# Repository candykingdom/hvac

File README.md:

# Playa engineering!

## Installing the breadboard in arduino

You have to install the board type "atmega328 on a breadboard". Follow the
instructions in [Minimal Circuit (Eliminating the External
Clock)](https://www.arduino.cc/en/Tutorial/ArduinoToBreadboard)

## Digikey components

Power:

[Sabre flat blade literature](http://www.literature.molex.com/SQLImages/kelmscott/Molex/PDF_Images/987650-5662.PDF)

For a 10 foot run @ 12v 4A, allowing for 3% voltage drop.

Wire Size           14 AWG
Voltage at Max Drop 11.64 V

 *  [Board Side](https://www.digikey.com/product-detail/en/molex-llc/0431601102/WM18483-ND/300116)
 *  [Cable Side](https://www.digikey.com/products/en?keywords=44441-2002)
 *  [Crimp](https://www.digikey.com/product-detail/en/molex-llc/0433750001/WM9174CT-ND/300126)

Motors:
 *  [Board Side](http://www.mouser.com/ProductDetail/Molex/43160-3106/?qs=sGAEpiMZZMs%252bGHln7q6pm%252bS0pk2Wo0XxzlBm66UhqE8%3d)
 *  [Cable Side](https://www.digikey.com/product-detail/en/molex-llc/0444412006/WM18467-ND/300100) # Find the cable side version
 *  Same crimps

Data:

 *  [Board Side](https://www.digikey.com/short/3nbvwp)
 *  [Cable Side](https://www.digikey.com/product-detail/en/molex-llc/0511030900/WM13237-ND/3262504)
 *  [Crimp](https://www.digikey.com/product-detail/en/molex-llc/0503518000/WM3320CT-ND/2405712)

More components:

 *  [Through hole potentiometer](https://www.digikey.com/product-detail/en/bourns-inc/PDB12-H4301-103BF/PDB12-H4301-103BF-ND/3780664)
 *  [Through hole toggle switch](https://www.digikey.com/product-detail/en/e-switch/100SP1T1B4M2QE/EG2355-ND/378824)
 *  [Pushbutton Switch (PVA-H2)](https://www.digikey.com/product-detail/en/c-k/Y17P12211FP/401-1135-ND/417718)
 *  [MOSFET](https://www.digikey.com/product-detail/en/nexperia-usa-inc/BUK9Y09-40B,115/1727-4611-1-ND/2531001)
 *  [Fuseholder](https://www.digikey.com/product-detail/en/keystone-electronics/3550-2/36-3550-2-ND/2137310)

TODO:
 *  Mounting holes for the face plate.
 *  Add labels for the switches and pots
 *  The timer button has pin 2 wired to the micro but in real life pin 3 should be it. i.e. the spec says the switches are horizontal but they are actually vertical.
 *  Switch to ARM
 *  The pins that were chosen for i2c turned out to be the same pins that were used for the crystal. The crystal pins required tedious manual intervention to interact with them.

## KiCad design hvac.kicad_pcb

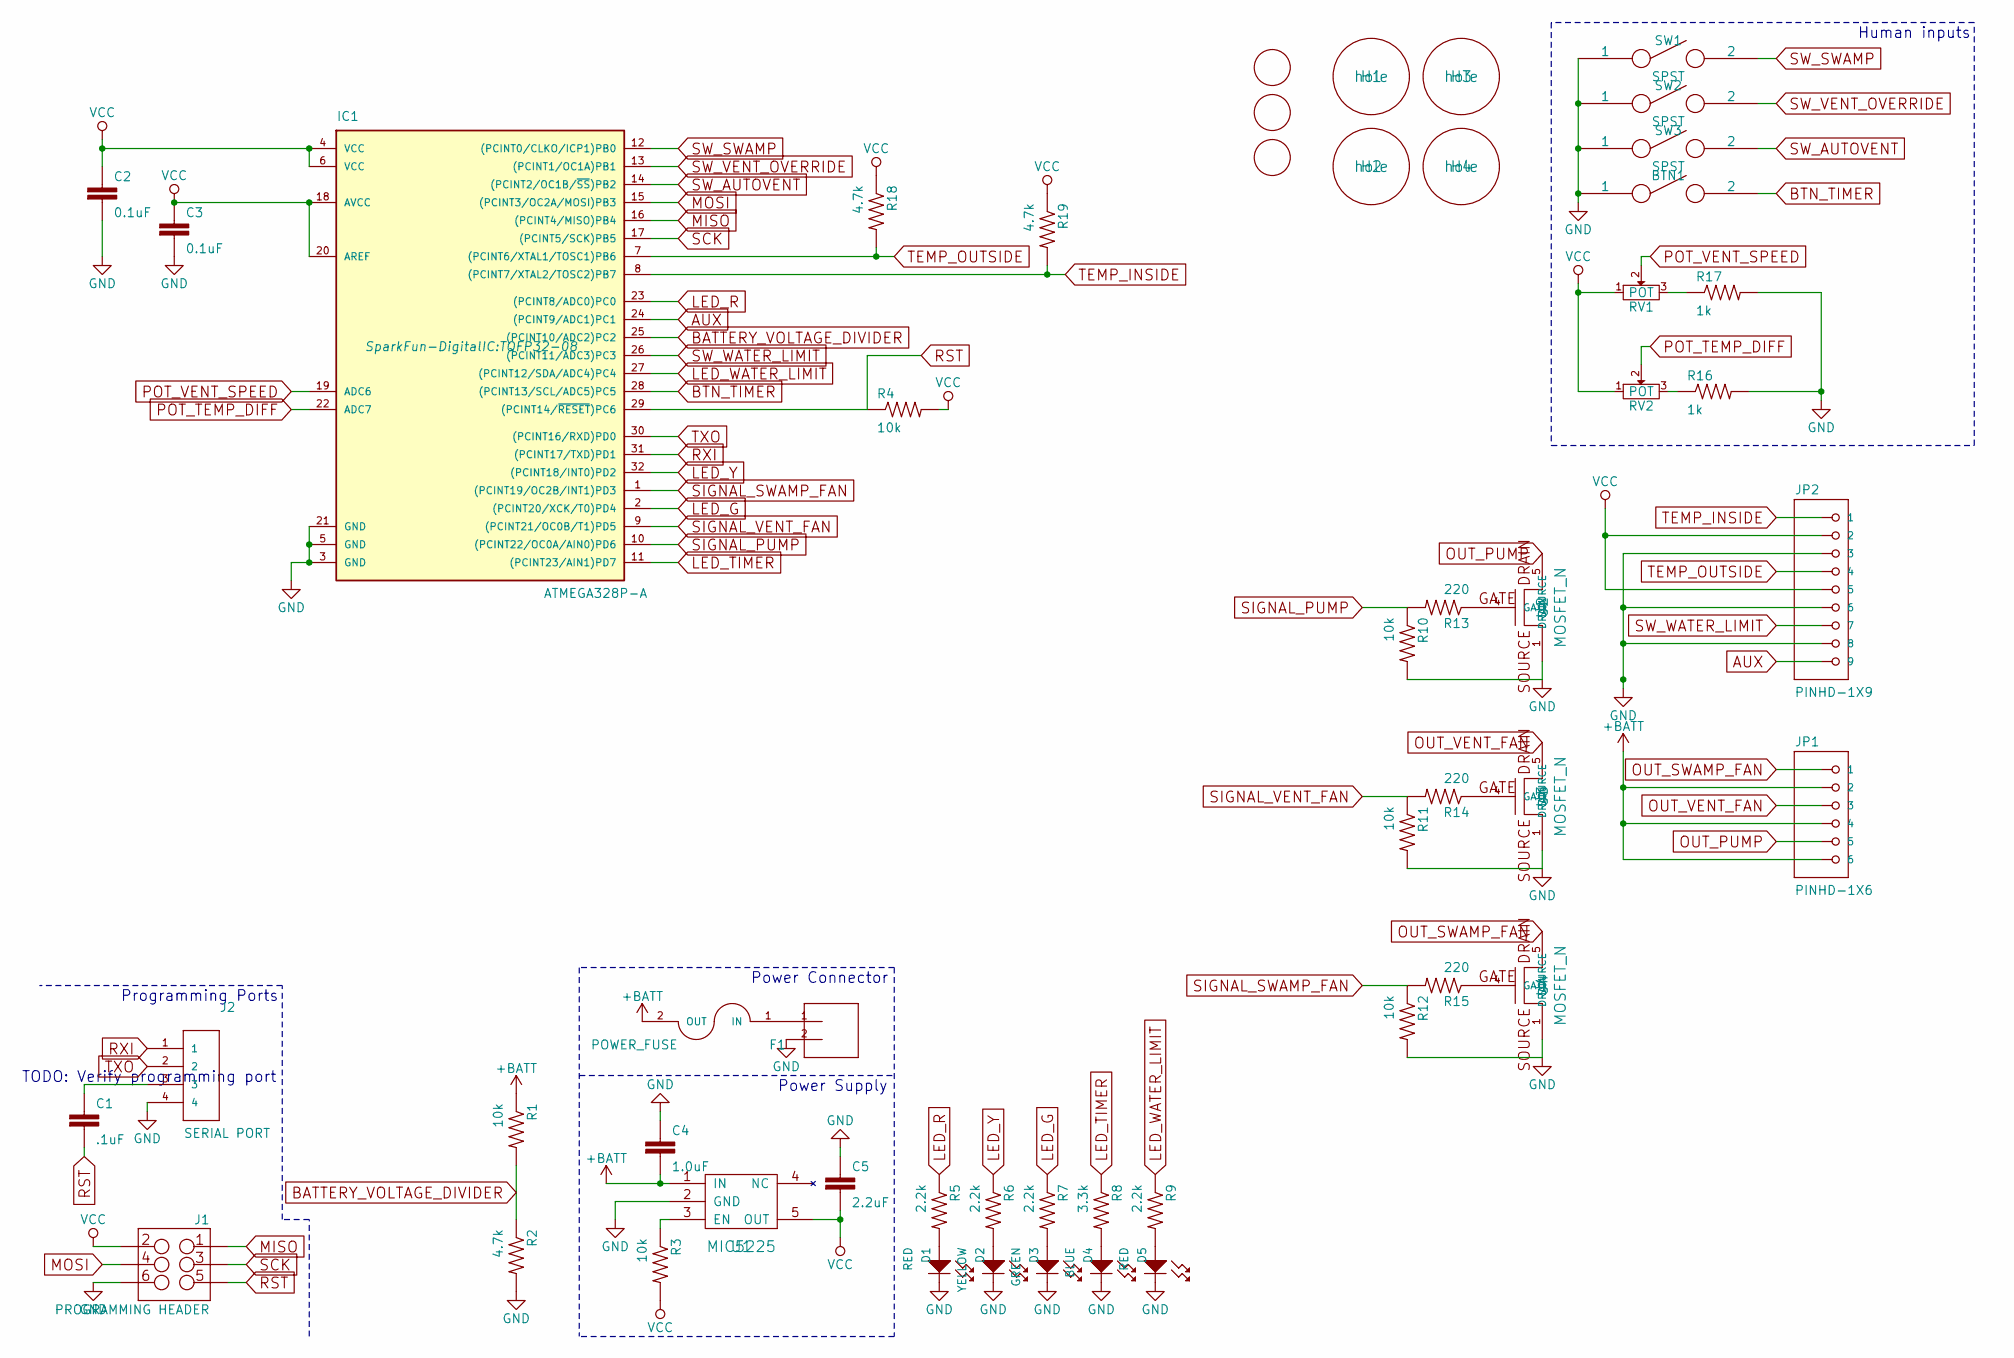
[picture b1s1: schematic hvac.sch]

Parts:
BTN1: SPST; PVA1-OA-H2
C1: .1uF; C_0603
C2, C3: 0.1uF; C_0603
C4: 1.0uF; C_0603
C5: 2.2uF; C_0603
D1, D5: RED; MF_LEDs-LED0603
D2: YELLOW; MF_LEDs-LED0603
D3: GREEN; MF_LEDs-LED0603
D4: BLUE; MF_LEDs-LED0603
F1: POWER_FUSE; FUSE-3550-2
H1, H2, H3, H4: hole; hole-m2.5
IC1: ATMEGA328P-A; TQFP32-08
J1: PROGRAMMING HEADER; 2X3
J2: SERIAL PORT; 1X04
J3: POWER_INPUT; 1x2-RIGHT_ANGLE-43160-1102
JP1: PINHD-1X6; 1x6-RIGHT_ANGLE-43160-3106
JP2: PINHD-1X9; 1x9-RIGHT_ANGLE-0534260910
M1, M2, M3: FIDUCIAL; FIDUCIAL_1MM
R1, R3, R4, R10, R11, R12: 10k; R_0402
R2, R18, R19: 4.7k; R_0402
R5, R6, R7, R9: 2.2k; R_0402
R8: 3.3k; R_0402
R13, R14, R15: 220; R_0402
R16, R17: 1k; R_0402
RV1, RV2: POT; PDB12-H4301-103BF
SW1, SW2, SW3: SPST; EG2355-ND
U1: MIC5225; SOT-23-5
U2, U3, U4: MOSFET_N; SOT-669_LFPAK_ThermalVias-1

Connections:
+BATT: C4.2, F1.2 (OUT), JP1.2, JP1.4, JP1.6, R1.1, U1.1 (IN)
AUX: IC1.24 ((PCINT9/ADC1)PC1), JP2.9
BATTERY_VOLTAGE_DIVIDER: IC1.25 ((PCINT10/ADC2)PC2), R1.2, R2.1
BTN_TIMER: BTN1.2, IC1.28 ((PCINT13/SCL/ADC5)PC5)
GND: BTN1.1, C2.2, C3.2, C4.1, C5.1, D1.CATH (CATHODE), D2.CATH (CATHODE), D3.CATH (CATHODE), D4.CATH (CATHODE), D5.CATH (CATHODE), IC1.3 (GND), IC1.5 (GND), IC1.21 (GND), J1.6, J2.4, J3.2, JP2.3, JP2.6, JP2.8, R2.2, R10.2, R11.2, R12.2, R16.2, R17.2, SW1.1, SW2.1, SW3.1, U1.2 (GND), U2.1 (SOURCE), U2.2 (SOURCE), U2.3 (SOURCE), U3.1 (SOURCE), U3.2 (SOURCE), U3.3 (SOURCE), U4.1 (SOURCE), U4.2 (SOURCE), U4.3 (SOURCE)
LED_G: IC1.2 ((PCINT20/XCK/T0)PD4), R7.1
LED_R: IC1.23 ((PCINT8/ADC0)PC0), R5.1
LED_TIMER: IC1.11 ((PCINT23/AIN1)PD7), R8.1
LED_WATER_LIMIT: IC1.27 ((PCINT12/SDA/ADC4)PC4), R9.1
LED_Y: IC1.32 ((PCINT18/INT0)PD2), R6.1
MISO: IC1.16 ((PCINT4/MISO)PB4), J1.1
MOSI: IC1.15 ((PCINT3/OC2A/MOSI)PB3), J1.4
unnamed: C1.1, J2.3
unnamed: D1.ANOD (ANODE), R5.2
unnamed: D2.ANOD (ANODE), R6.2
unnamed: D3.ANOD (ANODE), R7.2
unnamed: D4.ANOD (ANODE), R8.2
unnamed: D5.ANOD (ANODE), R9.2
unnamed: F1.1 (IN), J3.1
unnamed: R3.1, U1.3 (EN)
unnamed: R13.1, U2.4 (GATE)
unnamed: R14.1, U3.4 (GATE)
unnamed: R15.1, U4.4 (GATE)
unnamed: R16.1, RV2.3
unnamed: R17.1, RV1.3
OUT_PUMP: JP1.5, U2.5 (DRAIN)
OUT_SWAMP_FAN: JP1.1, U4.5 (DRAIN)
OUT_VENT_FAN: JP1.3, U3.5 (DRAIN)
POT_TEMP_DIFF: IC1.22 (ADC7), RV2.2
POT_VENT_SPEED: IC1.19 (ADC6), RV1.2
RST: C1.2, IC1.29 ((PCINT14/~RESET~)PC6), J1.5, R4.1
RXI: IC1.31 ((PCINT17/TXD)PD1), J2.1
SCK: IC1.17 ((PCINT5/SCK)PB5), J1.3
SIGNAL_PUMP: IC1.10 ((PCINT22/OC0A/AIN0)PD6), R10.1, R13.2
SIGNAL_SWAMP_FAN: IC1.1 ((PCINT19/OC2B/INT1)PD3), R12.1, R15.2
SIGNAL_VENT_FAN: IC1.9 ((PCINT21/OC0B/T1)PD5), R11.1, R14.2
SW_AUTOVENT: IC1.14 ((PCINT2/OC1B/~SS~)PB2), SW3.2
SW_SWAMP: IC1.12 ((PCINT0/CLKO/ICP1)PB0), SW1.2
SW_VENT_OVERRIDE: IC1.13 ((PCINT1/OC1A)PB1), SW2.2
SW_WATER_LIMIT: IC1.26 ((PCINT11/ADC3)PC3), JP2.7
TEMP_INSIDE: IC1.8 ((PCINT7/XTAL2/TOSC2)PB7), JP2.1, R19.2
TEMP_OUTSIDE: IC1.7 ((PCINT6/XTAL1/TOSC1)PB6), JP2.4, R18.2
TXO: IC1.30 ((PCINT16/RXD)PD0), J2.2
VCC: C2.1, C3.1, C5.2, IC1.4 (VCC), IC1.6 (VCC), IC1.18 (AVCC), IC1.20 (AREF), J1.2, JP2.2, JP2.5, R3.2, R4.2, R18.1, R19.1, RV1.1, RV2.1, U1.5 (OUT)

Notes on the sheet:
Power Supply
Human inputs
Power Connector
Programming Ports
TODO: Verify programming port

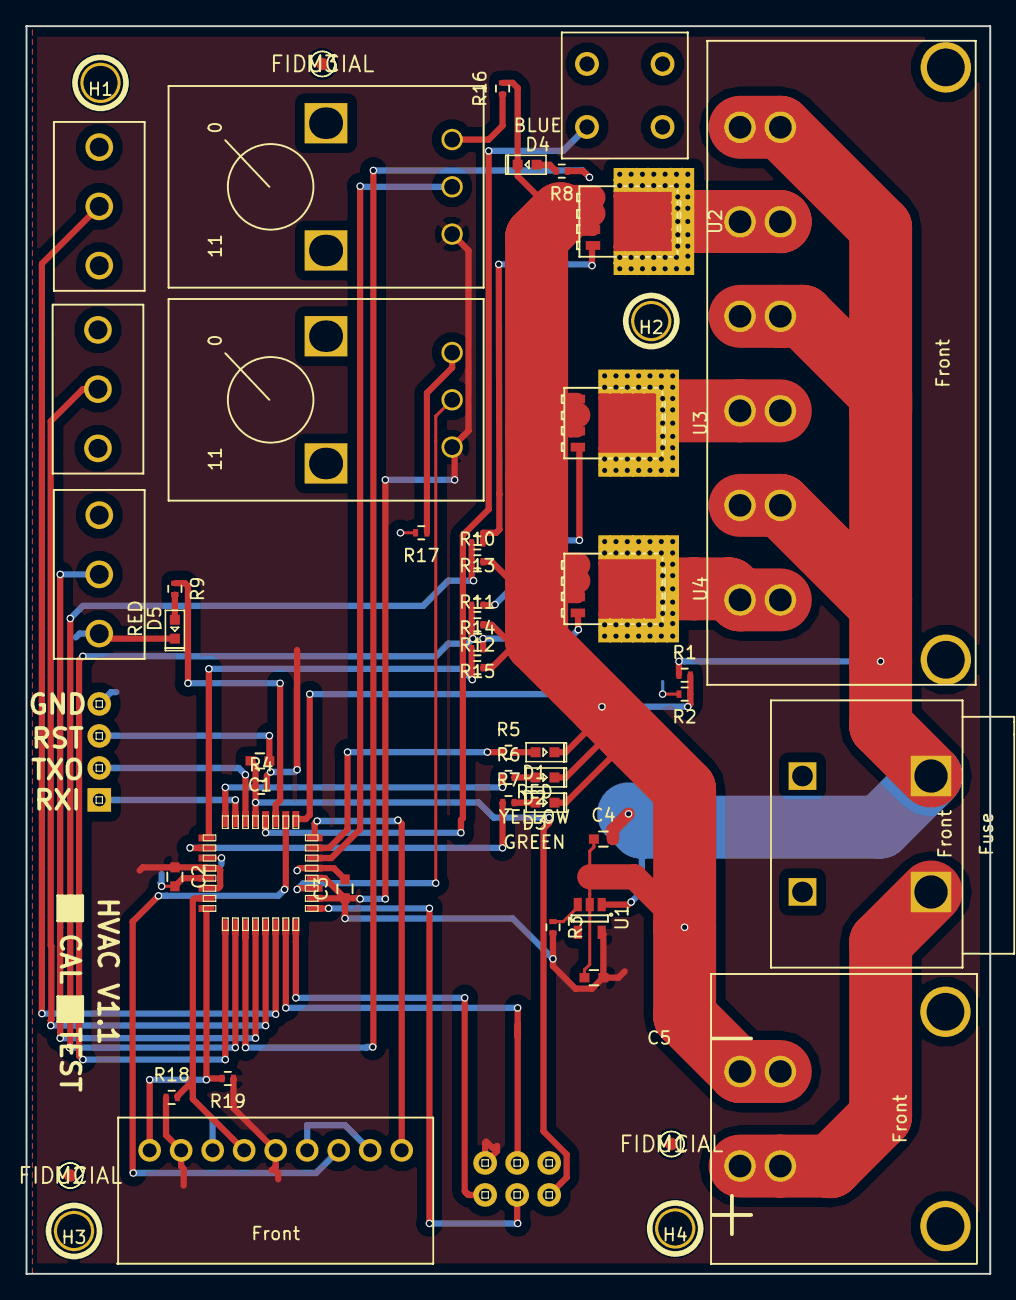
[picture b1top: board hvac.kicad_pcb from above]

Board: 2 copper layers, 76.5 x 99.0 mm, 53 parts (0 on the bottom side), 44 nets.

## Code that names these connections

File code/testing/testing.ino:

  #import "OneWire.h"

// http://www.hobbytronics.co.uk/arduino-atmega328-pinout
const int LED_R = A0; // PC0
const int LED_Y = 2; // PD2
const int LED_G = 4; // PD4
const int LED_WATER_LIMIT = A4; // PC4
const int LED_TIMER = 7; // PD7

const int SW_SWAMP = 8; // PB0
const int SW_VENT_OVERRIDE = 9; // PB1
const int SW_AUTOVENT = 10; // PB2

// http://www.instructables.com/id/22-Bit-Binary-Counter-for-Atmega328/
const int OUT_TEMP_PIN = 2; //PB6/PCINT6;
const int IN_TEMP_PIN = PCINT7;

// NOT VERIFIED  //PD3, // MOSFET Swamp fan
// NOT VERIFIED  //PD5, // MOSFET Vent fan
// NOT VERIFIED  //PD6  // MOSFET Pump

const int outputs[] = {
  LED_R,
  LED_Y,
  LED_G,

  LED_WATER_LIMIT,
  LED_TIMER
};


const int inputs[] = {
  OUT_TEMP_PIN,
  IN_TEMP_PIN
};

const int pullup_inputs[] = {
  SW_SWAMP,
  SW_VENT_OVERRIDE,
  SW_AUTOVENT
};

const float SOURCE_VOLTAGE = 5.0; // TODO: measure that
const float HIGH_DEAD_BAND_PERCENTAGE = 0.0;
const float LOW_DEAD_BAND_PERCENTAGE = 0.0;
// (V_s * R_2) / (R_1 + R_2) = V_out
const float POT_VOLTAGE_HIGH = (SOURCE_VOLTAGE * 10000) / (1000 + 10000) - (HIGH_DEAD_BAND_PERCENTAGE * SOURCE_VOLTAGE);
const float POT_VOLTAGE_LOW  = (SOURCE_VOLTAGE * 10)    / (1000 + 10)    + ( LOW_DEAD_BAND_PERCENTAGE * SOURCE_VOLTAGE);
const long POT_VALUE_HIGH = (POT_VOLTAGE_HIGH / SOURCE_VOLTAGE) * 1023;
const long POT_VALUE_LOW  = (POT_VOLTAGE_LOW / SOURCE_VOLTAGE) * 1023;

OneWire * inTempSensor;
OneWire * outTempSensor;


void setup() {
  Serial.begin(9600);
  
  // put your setup code here, to run once:
  for(int i = 0; i < sizeof(outputs); i++) {
    int output = outputs[i];
    pinMode(output, OUTPUT);
    digitalWrite(output, LOW);
  }

  for(int i = 0; i < sizeof(inputs); i++) {
    int input = inputs[i];
    pinMode(input, INPUT);
  }
  
  for(int i = 0; i < sizeof(pullup_inputs); i++) {
    int input = pullup_inputs[i];
    pinMode(input, INPUT_PULLUP);
  }

  // Set up onewire pins
  //OneWire( uint8_t pinArg, uint8_t portArg, uint8_t bitmaskArg, uint8_t *outputRegArg, uint8_t *inputRegArg, uint8_t *modeRegArg);
  uint8_t pinArg        = IN_TEMP_PIN;
  uint8_t bitmaskArg    = 1 << 6;    // PB7... so 7 // digitalPinToBitMask(pin);
  uint8_t *outputRegArg = &PORTB;    // portOutputRegister(port);
  uint8_t *inputRegArg  = &PINB;     // portInputRegister(port);
  uint8_t *modeRegArg   = &DDRB;     // portModeRegister(port);
  inTempSensor = new OneWire(pinArg, bitmaskArg, outputRegArg, inputRegArg, modeRegArg);

  pinArg        = OUT_TEMP_PIN;
  bitmaskArg    = 1 << 4;    // PB6... so 6 // digitalPinToBitMask(pin);
  outputRegArg  = &PORTC;    // portOutputRegister(port);
  inputRegArg   = &PINC;     // portInputRegister(port);
  modeRegArg    = &DDRC;     // portModeRegister(port);
  outTempSensor = new OneWire(pinArg, bitmaskArg, outputRegArg, inputRegArg, modeRegArg);
  // Turn on to prove a point... what point I'm not sure.
  DDRC = 0b11111111;
  PORTC = 0b11111111;
  outTempSensor->digiWrite(1);
    
  digitalWrite(LED_R, HIGH);
  digitalWrite(LED_Y, LOW);
  digitalWrite(LED_G, LOW);
  pause();
  digitalWrite(LED_Y, HIGH);
  pause();
  digitalWrite(LED_G, HIGH);
  pause();
  digitalWrite(LED_R, LOW);
  digitalWrite(LED_Y, LOW);
  digitalWrite(LED_G, LOW);
  pause();

  digitalWrite(LED_TIMER, HIGH);

  // Datasheet 18.2.3. 
  //DDRB = 0b00000000;
  //PORTB = 0b11111111;
}

void pause() {
  delay(20);
}

void red() {
  digitalWrite(LED_G, LOW);
  //digitalWrite(LED_Y, LOW);
  digitalWrite(LED_R, HIGH);
}
void yellow() {
  digitalWrite(LED_R, LOW);
  digitalWrite(LED_G, LOW);
  digitalWrite(LED_Y, HIGH);
}
void green() {
  digitalWrite(LED_R, LOW);
  //digitalWrite(LED_Y, LOW);
  digitalWrite(LED_G, HIGH);
}

bool b = false;
bool y = false;
void loop() {
  Serial.println("Testing");
  //DDRC = 0b11111111;
  //PORTC = 0b11111111;
  //outTempSensor->digiWrite(1);

  //outTempSensor->digiWrite(inTempSensor->digiRead());
/*
  int temp = 0;
  //temp = inTempSensor->getTemp();
  for (float i = 0; i < temp; i++) {
    //digitalWrite(LED_Y, y = !y);
    outTempSensor->digiWrite(1);
    digitalWrite(LED_Y, y = !y);
    delay(100);
  }
  outTempSensor->digiWrite(1);
  delay(100);
  outTempSensor->digiWrite(0);
  digitalWrite(LED_TIMER, b = !b);
  delay(500);
/**/}  

/*  
  int button;
  //button = digitalRead(SW_SWAMP);
  button = digitalRead(SW_AUTOVENT);
  //button = digitalRead(SW_VENT_OVERRIDE);
  if (button == HIGH) {
    green();
  } else {
    red();
  }
*/
  /*if (temp < 64) {
    //if (temp > -1) {
      //Serial.print("A");
    //}
  //}
  /** /
  for(int i = 0; i < sizeof(pins); i++) {
    int PIN = pins[i];
    // put your main code here, to run repeatedly:
    digitalWrite(PIN, HIGH);
  }
  pause();
  for(int i = 0; i < sizeof(pins); i++) {
    int PIN = pins[i];
    // Turn off all the pins (disabled for testing)
    //digitalWrite(PIN, LOW);
  }
  pause();
  /**/

  /** Read from the pot * /
  long value = analogRead(POT_VENT);
  if (value < POT_VALUE_LOW) {
    red();
  }  else if (value < ((POT_VALUE_LOW + POT_VALUE_HIGH) / 2)) {
    yellow();
  } else {
    green();
  }
  }
  /**/

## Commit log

2017-05-06 Add kicad files
2017-05-07 Add MIC5225 to homebrew and place power supply on board
2017-05-07 Save some links from digikey for components
2017-05-07 Add components
    * Add power supply
    * Add LEDs
    * Add Serial
    * Add programming header
2017-05-07 Wire up inputs and outputs
2017-05-07 Hook up all components and fix warnings
    TODO: Set up output stages
2017-05-07 Add mosfets for driving fans and pump
2017-05-07 Switch to 220ohm resistors
2017-05-07 Add rendering
2017-05-07 Add notes on connectors
2017-05-07 Switch to 6 pin header
2017-05-07 Switch to 9 pin header and provide ground/vcc for every temp sensor
2017-05-07 Add a part for EG2355-ND (throw switch)
2017-05-08 Add some footprints
2017-05-08 Give things better names
2017-05-08 Begin routing
2017-06-07 Lay out all the parts in semi logical places
2017-06-07 Create hole footprint and route a few small things
2017-06-07 Add holes to the pcb layout
2017-06-07 Add fiducials to the board for the pick n place
2017-06-07 Partial routing
2017-06-07 More routing
2017-06-11 First pass routing everything
2017-06-11 Fix remaining DRC errors
2017-06-11 Generate gerber files per macrofab instructions
    https://macrofab.com/help/creating-managing-ordering-pcbs/creating-pcb-projects-kicad/
2017-06-11 Add version info to the board
2017-06-11 Regenerate gerber files
2017-07-11 Post build notes
2017-07-12 Move pieces to fit better
2017-07-12 Add pullup resistors for temperature probes
2017-07-12 Bump revision + minor changes
2018-07-21 Saving last years changes... dunno
